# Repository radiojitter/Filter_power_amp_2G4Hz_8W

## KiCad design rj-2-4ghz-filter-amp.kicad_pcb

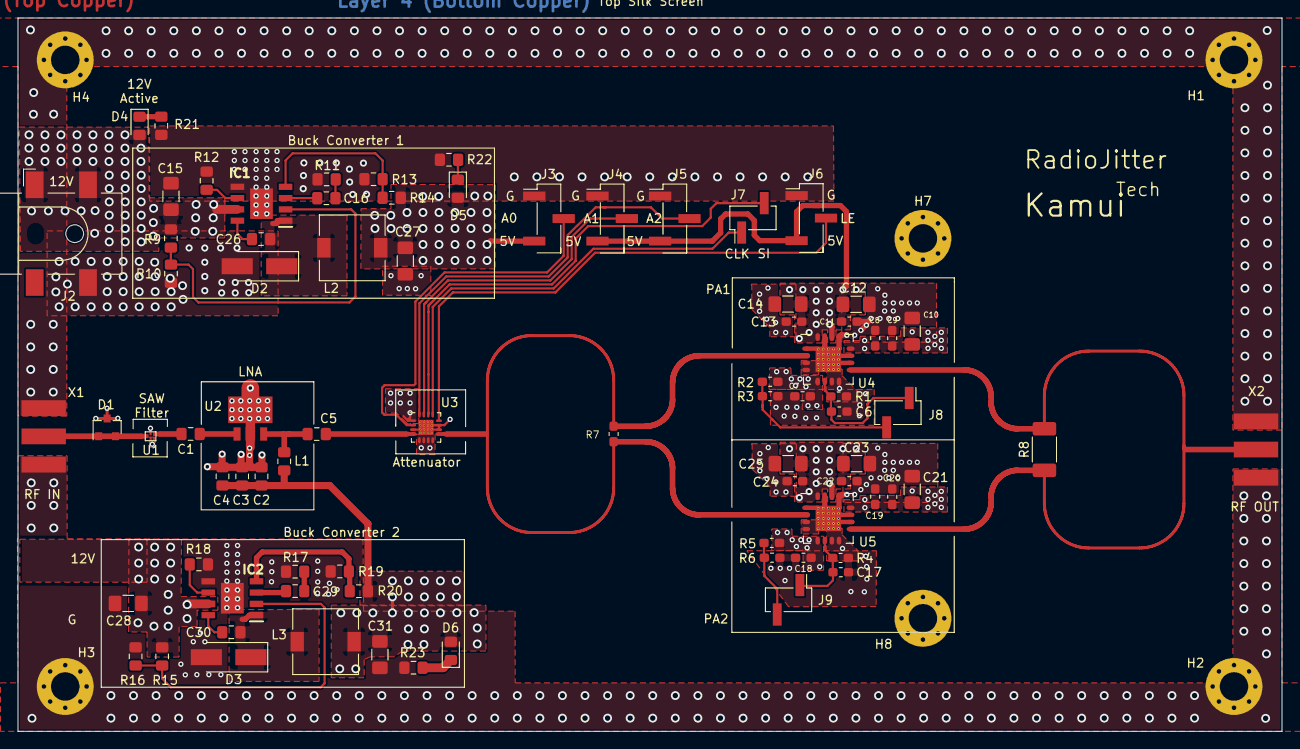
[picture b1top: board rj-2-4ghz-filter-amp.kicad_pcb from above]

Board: 4 copper layers, 142.2 x 80.3 mm, 86 parts (0 on the bottom side), 38 nets.

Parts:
C1, C4, C5: 68pF; C_0805_2012Metric_Pad1.15x1.40mm_HandSolder
C2: 1uF; C_0805_2012Metric_Pad1.15x1.40mm_HandSolder
C3: 1200pF; C_0805_2012Metric_Pad1.15x1.40mm_HandSolder
C6, C9, C11, C13, C17, C20, C22, C24: 3.3n; C_0603_1608Metric_Pad1.05x0.95mm_HandSolder
C7, C18: 1u; C_0603_1608Metric_Pad1.05x0.95mm_HandSolder
C8, C19: 100p; C_0603_1608Metric_Pad1.05x0.95mm_HandSolder
C10, C12, C14, C21, C23, C25: 10u; C_1206_3216Metric_Pad1.42x1.75mm_HandSolder
C15, C27, C28, C31: 10uF; C_1206_3216Metric_Pad1.42x1.75mm_HandSolder
C16, C29: 150pF; C_0805_2012Metric_Pad1.15x1.40mm_HandSolder
C26, C30: 0.1uF; C_0805_2012Metric_Pad1.15x1.40mm_HandSolder
D1: BAV99; SOT-23
D2, D3: SS34; D_SMA_Handsoldering
D4, D5, D6: RED; LED_0805_2012Metric_Pad1.15x1.40mm_HandSolder
H1, H2, H3, H4, H7, H8: MountingHole_Pad; MountingHole_3.2mm_M3_Pad_Via
IC1, IC2: MP1584EN-LF-Z; SOIC127P600X170-9N
J2: Barrel_Jack; BarrelJack_CLIFF_FC681465S_SMT_Horizontal
J3, J4, J5, J6: Conn_01x03; PinHeader_1x03_P2.54mm_Vertical_SMD_Pin1Left
J7, J8, J9: Conn_01x02; PinHeader_1x02_P2.54mm_Vertical_SMD_Pin1Left
L1: 82nH; L_0805_2012Metric_Pad1.15x1.40mm_HandSolder
L2, L3: 15uH; L_7.3x7.3_H4.5
R1, R4: 200k; R_0603_1608Metric_Pad1.05x0.95mm_HandSolder
R2, R5: 15k; R_0603_1608Metric_Pad1.05x0.95mm_HandSolder
R3, R6: 10k; R_0603_1608Metric_Pad1.05x0.95mm_HandSolder
R7: 100; R_0603_1608Metric_Pad1.05x0.95mm_HandSolder
R8: 100; R_2010_5025Metric_Pad1.52x2.65mm_HandSolder
R9, R11, R12, R15, R17, R18: 100K; R_0805_2012Metric_Pad1.15x1.40mm_HandSolder
R10, R16: 24.9K; R_0805_2012Metric_Pad1.15x1.40mm_HandSolder
R13, R19: 40.2K; R_0805_2012Metric_Pad1.15x1.40mm_HandSolder
R14, R20, R21, R22, R23: 210K; R_0805_2012Metric_Pad1.15x1.40mm_HandSolder
U1: B39242B4360P810
U2: SPF5189Z
U3: RFSA3613
U4, U5: SKY66295; SKY66292-11
X1, X2: SMA-; SMA_India_Local

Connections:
/5V_B1: C7.1, C8.1, C9.1, C10.1, C11.1, C12.1, C13.1, C14.1, C27.1, D5.2, J3.3, J4.3, J5.3, J6.3, L2.2, R2.1, R14.2, U3.1, U4.5, U4.12, U4.14, U4.16
/5V_B2: C2.1, C3.1, C4.1, C18.1, C19.1, C20.1, C21.1, C22.1, C23.1, C24.1, C25.1, C31.1, D6.2, L1.1, L3.2, R5.1, R20.2, U5.5, U5.12, U5.14, U5.16
/Buck 1 5v/PWR_IN: C15.1, C28.1, D4.2, IC1.7, IC2.7, J2.1, R9.1, R15.1
/High Power Ampifier/RF_IN: R7.1, R7.2, U3.9, U4.2, U5.2
/High Power Ampifier/RF_OUT: R8.1, R8.2, U4.9, U5.9, X2.1
/LNA/RF_IN: C1.1, U1.4
/RF Attenuator/A0: J3.2, U3.2
/RF Attenuator/A1: J4.2, U3.15
/RF Attenuator/A2: J5.2, U3.16
/RF Attenuator/CLK: J7.1, U3.13
/RF Attenuator/LE: J6.2, U3.12
/RF Attenuator/RF_IN: C5.2, U3.4
/RF Attenuator/SI: J7.2, U3.14
/Saw Filter/RF_IN: D1.1, D1.2, U1.1, X1.1
GND: C2.2, C3.2, C4.2, C6.2, C7.2, C8.2, C9.2, C10.2, C11.2, C12.2, C13.2, C14.2, C15.2, C17.2, C18.2, C19.2, C20.2, C21.2, C22.2, C23.2, C24.2, C25.2, C27.2, C28.2, C31.2, D1.3, D2.2, D3.2, H1.1, H2.1, H3.1, H4.1, H7.1, H8.1, IC1.5, IC1.9, IC2.5, IC2.9, J2.2, J3.1, J4.1, J5.1, J6.1, R1.2, R3.2, R4.2, R6.2, R10.2, R11.2, R12.2, R13.2, R16.2, R17.2, R18.2, R19.2, R21.2, R22.2, R23.2, U1.2, U1.3, U1.5, U2.2, U2.4, U3.3, U3.5, U3.6, U3.7, U3.8, U3.10, U3.11, U3.17, U4.1, U4.3, U4.4, U4.7, U4.8, U4.10, U4.11, U4.13, U4.15, U4.17, U5.1, U5.3, U5.4, U5.7, U5.8, U5.10, U5.11, U5.13, U5.15, U5.17, X1.2, X2.2
unnamed: C1.2, U2.1
unnamed: C5.1, L1.2, U2.3
unnamed: C6.1, J8.1, R1.1, U4.6
unnamed: C16.1, IC1.3
unnamed: C16.2, R11.1
unnamed: C17.1, J9.1, R4.1, U5.6
unnamed: C26.1, D2.1, IC1.1, L2.1
unnamed: C26.2, IC1.8
unnamed: C29.1, IC2.3
unnamed: C29.2, R17.1
unnamed: C30.1, D3.1, IC2.1, L3.1
unnamed: C30.2, IC2.8
unnamed: D4.1, R21.1
unnamed: D5.1, R22.1
unnamed: D6.1, R23.1
unnamed: IC1.2, R9.2, R10.1
unnamed: IC1.4, R13.1, R14.1
unnamed: IC1.6, R12.1
unnamed: IC2.2, R15.2, R16.1
unnamed: IC2.4, R19.1, R20.1
unnamed: IC2.6, R18.1
unnamed: J8.2, R2.2, R3.1
unnamed: J9.2, R5.2, R6.1

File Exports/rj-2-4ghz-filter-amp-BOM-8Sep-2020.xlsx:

Column1 | Column2 | Column3 | Column4 | Column5 | Column6 | Column7
Ref | Qnty | Value | Cmp name | Footprint | Description | Vendor
C1, C4, C5, | 3 | 68pF | C | Capacitor_SMD:C_0805_2012Metric_Pad1.15x1.40mm_HandSolder | Unpolarized capacitor
C2, | 1 | 1uF | C | Capacitor_SMD:C_0805_2012Metric_Pad1.15x1.40mm_HandSolder | Unpolarized capacitor
C3, | 1 | 1200pF | C | Capacitor_SMD:C_0805_2012Metric_Pad1.15x1.40mm_HandSolder | Unpolarized capacitor
C6, C9, C11, C13, C17, C20, C22, C24, | 8 | 3.3n | C | Capacitor_SMD:C_0603_1608Metric_Pad1.05x0.95mm_HandSolder | Unpolarized capacitor
C7, C18, | 2 | 1u | C | Capacitor_SMD:C_0603_1608Metric_Pad1.05x0.95mm_HandSolder | Unpolarized capacitor
C8, C19, | 2 | 100p | C | Capacitor_SMD:C_0603_1608Metric_Pad1.05x0.95mm_HandSolder | Unpolarized capacitor
C10, C12, C14, C21, C23, C25, | 6 | 10u | C | Capacitor_SMD:C_1206_3216Metric_Pad1.42x1.75mm_HandSolder | Unpolarized capacitor
C15, C27, C28, C31, | 4 | 10uF | C | Capacitor_SMD:C_1206_3216Metric_Pad1.42x1.75mm_HandSolder | Unpolarized capacitor
C16, C29, | 2 | 150pF | C | Capacitor_SMD:C_0805_2012Metric_Pad1.15x1.40mm_HandSolder | Unpolarized capacitor
C26, C30, | 2 | 0.1uF | C | Capacitor_SMD:C_0805_2012Metric_Pad1.15x1.40mm_HandSolder | Unpolarized capacitor
D1, | 1 | BAV99 | BAV99-Diode | Package_TO_SOT_SMD:SOT-23
D2, D3, | 2 | SS34 | D_Schottky | Diode_SMD:D_SMA_Handsoldering | Schottky diode
D4, D5, D6, | 3 | RED | LED | LED_SMD:LED_0805_2012Metric_Pad1.15x1.40mm_HandSolder | Light emitting diode
H1, H2, H3, H4, H7, H8, | 6 | MountingHole_Pad | MountingHole_Pad | MountingHole:MountingHole_3.2mm_M3_Pad_Via | Mounting Hole with connection
IC1, IC2, | 2 | MP1584EN-LF-Z | MP1584EN-LF-Z | SOIC127P600X170-9N | Switching Voltage Regulators 3A 1.5MHz 28V Nonsync Buck
J2, | 1 | Barrel_Jack | Barrel_Jack | Connector_BarrelJack:BarrelJack_CLIFF_FC681465S_SMT_Horizontal | DC Barrel Jack
J3, J4, J5, J6, | 4 | Conn_01x03 | Conn_01x03 | Connector_PinHeader_2.54mm:PinHeader_1x03_P2.54mm_Vertical_SMD_Pin1Left | Generic connector, single row, 01x03, script generated (kicad-library-utils/sch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
J7, J8, J9, | 3 | Conn_01x02 | Conn_01x02 | Connector_PinHeader_2.54mm:PinHeader_1x02_P2.54mm_Vertical_SMD_Pin1Left | Generic connector, single row, 01x02, script generated (kicad-library-utils/sch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
L1, | 1 | 82nH | L | Inductor_SMD:L_0805_2012Metric_Pad1.15x1.40mm_HandSolder | Inductor
L2, L3, | 2 | 15uH | L | Inductor_SMD:L_7.3x7.3_H4.5 | Inductor
R1, R4, | 2 | 200k | R | Resistor_SMD:R_0603_1608Metric_Pad1.05x0.95mm_HandSolder | Resistor
R2, R5, | 2 | 15k | R | Resistor_SMD:R_0603_1608Metric_Pad1.05x0.95mm_HandSolder | Resistor
R3, R6, | 2 | 10k | R | Resistor_SMD:R_0603_1608Metric_Pad1.05x0.95mm_HandSolder | Resistor
R7, | 1 | 100 | R | Resistor_SMD:R_0603_1608Metric_Pad1.05x0.95mm_HandSolder | Resistor
R8, | 1 | 100 | R | Resistor_SMD:R_2010_5025Metric_Pad1.52x2.65mm_HandSolder | Resistor
R9, R11, R12, R15, R17, R18, | 6 | 100K | R | Resistor_SMD:R_0805_2012Metric_Pad1.15x1.40mm_HandSolder | Resistor
R10, R16, | 2 | 24.9K | R | Resistor_SMD:R_0805_2012Metric_Pad1.15x1.40mm_HandSolder | Resistor
R13, R19, | 2 | 40.2K | R | Resistor_SMD:R_0805_2012Metric_Pad1.15x1.40mm_HandSolder | Resistor
R14, R20, R21, R22, R23, | 5 | 210K | R | Resistor_SMD:R_0805_2012Metric_Pad1.15x1.40mm_HandSolder | Resistor
U1, | 1 | B39242B4360P810 | B39242B4360P810 | B39242B4360P810:B39242B4360P810
U2, | 1 | SPF5189Z | SBB5089Z-vk_custom_kicad | SPF5189Z:SPF5189Z
U3, | 1 | RFSA3613 | RFSA3613 | RFSA3613:RFSA3613
U4, U5, | 2 | SKY66295 | SKY66295-baum_rfParts-2-4GHzPA-rescue | SKY66292-11:SKY66292-11
X1, X2, | 2 | SMA- | SMA--vk_custom_kicad | VK_Cus_KiCad:SMA_India_Local

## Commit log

2020-08-23 upto PCB done
2020-09-06 done till all routing ground ring and ground plane handeled, only bare copper part is left
2020-09-06 hole positionsing and few via fixing
2020-09-06 adds bare copper
2020-09-08 adds annotations
2020-09-08 gerber and bom generated
2020-10-21 minor updates
